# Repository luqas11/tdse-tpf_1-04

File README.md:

# Proyecto Final
Este proyecto es el diseño de software y hardware para un **sistema de control de una máquina expendedora de bebidas**, proyecto final de la materia Taller de Sistemas Embebidos de la FIUBA.

## Notas
Para depurar el proyecto, se deben realizar las siguientes configuraciones en el STM32CubeIDE:
1. Run -> Debug configurations -> Debugger -> Debug Probe -> ST-LINK (OpenOCD) -> Apply
2. Run -> Debug configurations -> Debugger -> Show generator options -> Reset Mode -> Software system reset -> Apply
3. Run -> Debug configurations -> Startup -> Initialization Commands -> Escribir `monitor arm semihosting enable` -> Apply

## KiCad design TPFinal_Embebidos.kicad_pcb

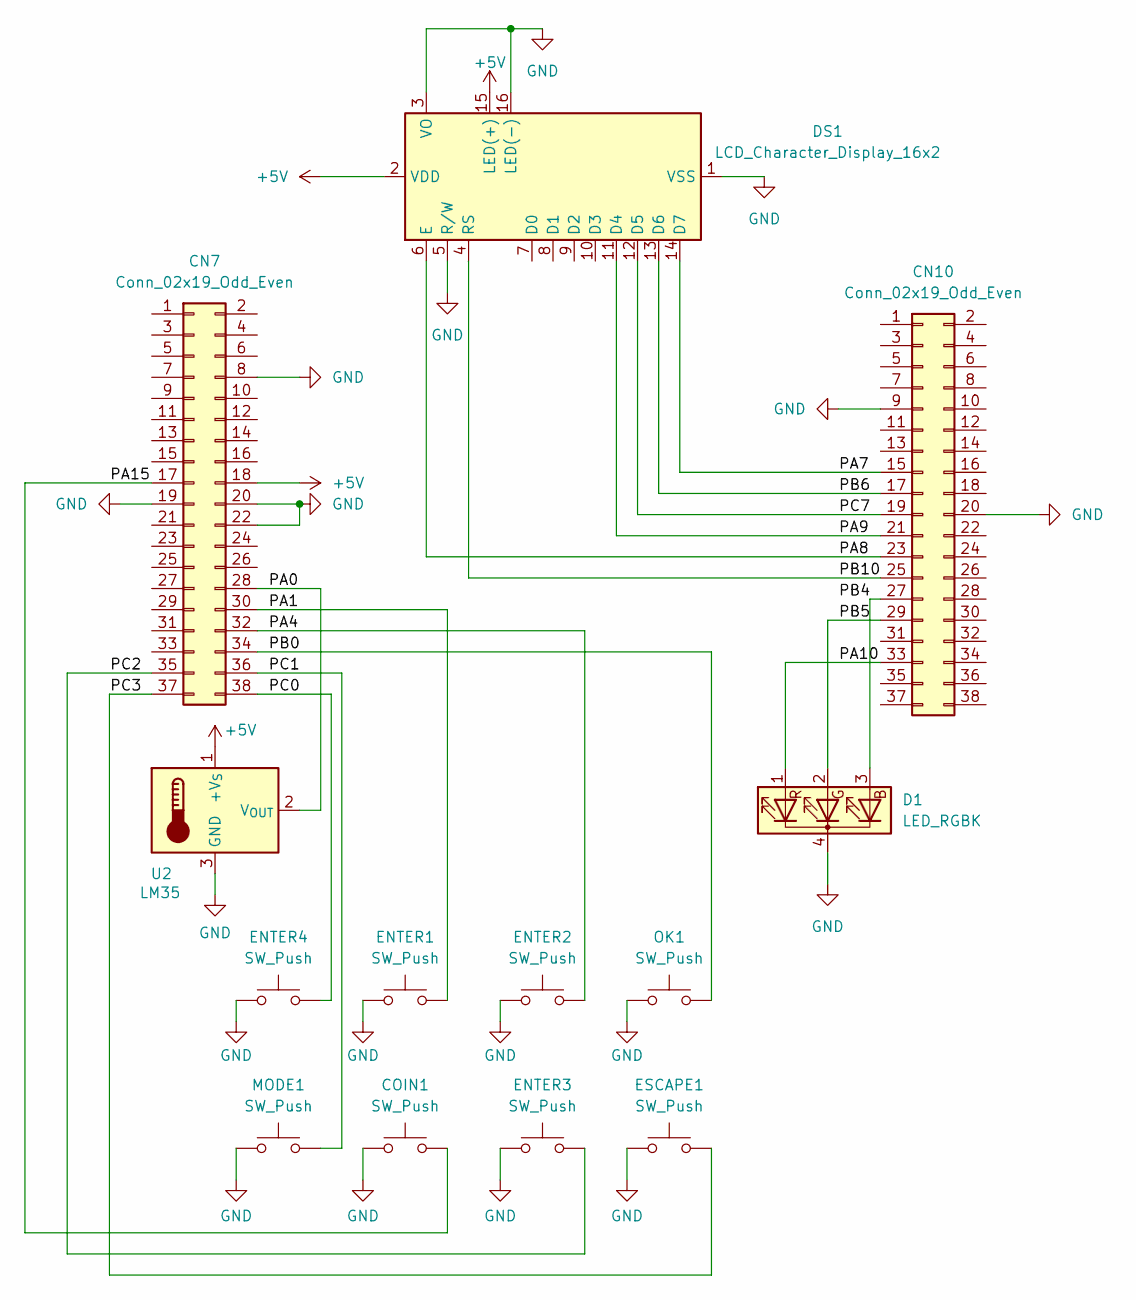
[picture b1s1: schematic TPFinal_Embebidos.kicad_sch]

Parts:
CN7, CN10: Conn_02x19_Odd_Even; PinSocket_2x19_P2.54mm_Vertical
COIN1: SW_Push; SW_PUSH_6mm_H7.3mm
D1: LED_RGBK; LED_D5.0mm-4_RGB_Wide_Pins
DS1: LCD_Character_Display_16x2; WC1602A
ENTER1, ENTER2, ENTER3, ENTER4: SW_Push; SW_PUSH_6mm_H7.3mm
ESCAPE1: SW_Push; SW_PUSH_6mm_H7.3mm
MODE1: SW_Push; SW_PUSH_6mm_H7.3mm
OK1: SW_Push; SW_PUSH_6mm_H7.3mm
U2: LM35; TO-92_Inline_Wide

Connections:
+5V: CN7.18, DS1.2 (VDD), DS1.15 (LED(+)), U2.1 (+V_{S})
/PA0: CN7.28, U2.2 (V_{OUT})
/PA1: CN7.30, ENTER1.2
/PA4: CN7.32, ENTER2.2
/PA7: CN10.15, DS1.14 (D7)
/PA8: CN10.23, DS1.6 (E)
/PA9: CN10.21, DS1.11 (D4)
/PA10: CN10.33, D1.1 (RA)
/PA15: CN7.17, COIN1.2
/PB0: CN7.34, OK1.2
/PB5: CN10.29, D1.2 (GA)
/PB6: CN10.17, DS1.13 (D6)
/PB10: CN10.25, DS1.4 (RS)
/PC0: CN7.38, ENTER4.2
/PC1: CN7.36, MODE1.2
/PC2: CN7.35, ENTER3.2
/PC3: CN7.37, ESCAPE1.2
/PC7: CN10.19, DS1.12 (D5)
GND: CN7.8, CN7.19, CN7.20, CN7.22, CN10.9, CN10.20, COIN1.1, D1.4 (K), DS1.1 (VSS), DS1.3 (VO), DS1.5 (R/W), DS1.16 (LED(-)), ENTER1.1, ENTER2.1, ENTER3.1, ENTER4.1, ESCAPE1.1, MODE1.1, OK1.1, U2.3 (GND)
unnamed: CN10.27, D1.3 (BA)

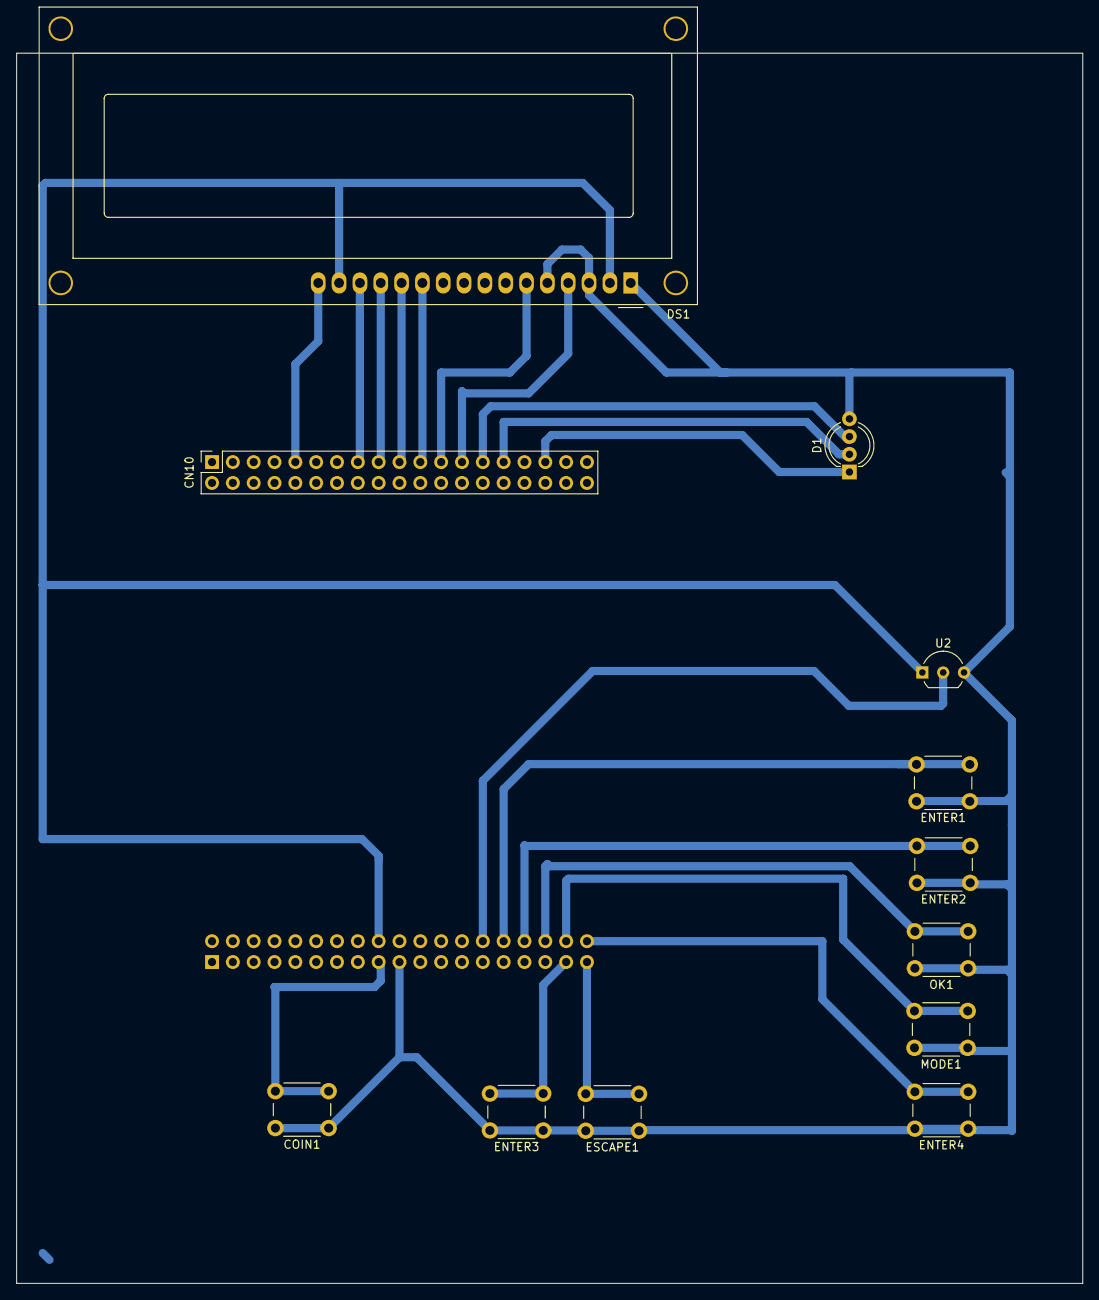
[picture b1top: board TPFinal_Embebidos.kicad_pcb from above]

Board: 2 copper layers, 130.0 x 150.0 mm, 13 parts (1 on the bottom side), 20 nets.

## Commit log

2025-07-25 Remove empty folder
2025-07-25 Add STM project
2025-07-28 Add buttons inputs configurations
2025-07-28 Add autoupdated files
2025-07-28 Add LED and display pin configuration
2025-07-29 Add temperature sensor reading
2025-08-02 Change pins assignments
2025-08-02 Update events names
2025-08-02 Implement operator menu
2025-08-03 Complete user menu
2025-08-03 Simplify display messages code
2025-08-03 Fix stock and price limits
2025-08-03 Add error state
2025-08-03 Fix wrong validation
2025-08-03 Remove metadata folder
2025-08-03 Add metadata folder to gitignore
2025-08-03 Add flash value saving logic
2025-08-03 Fix flash value saving
2025-08-03 Change pins to simplify PCB design
2025-08-12 Rename project
2025-08-13 Add project documentation
2025-08-13 Remove unnecessary files
2025-08-13 Add gitignore for KiCad project
